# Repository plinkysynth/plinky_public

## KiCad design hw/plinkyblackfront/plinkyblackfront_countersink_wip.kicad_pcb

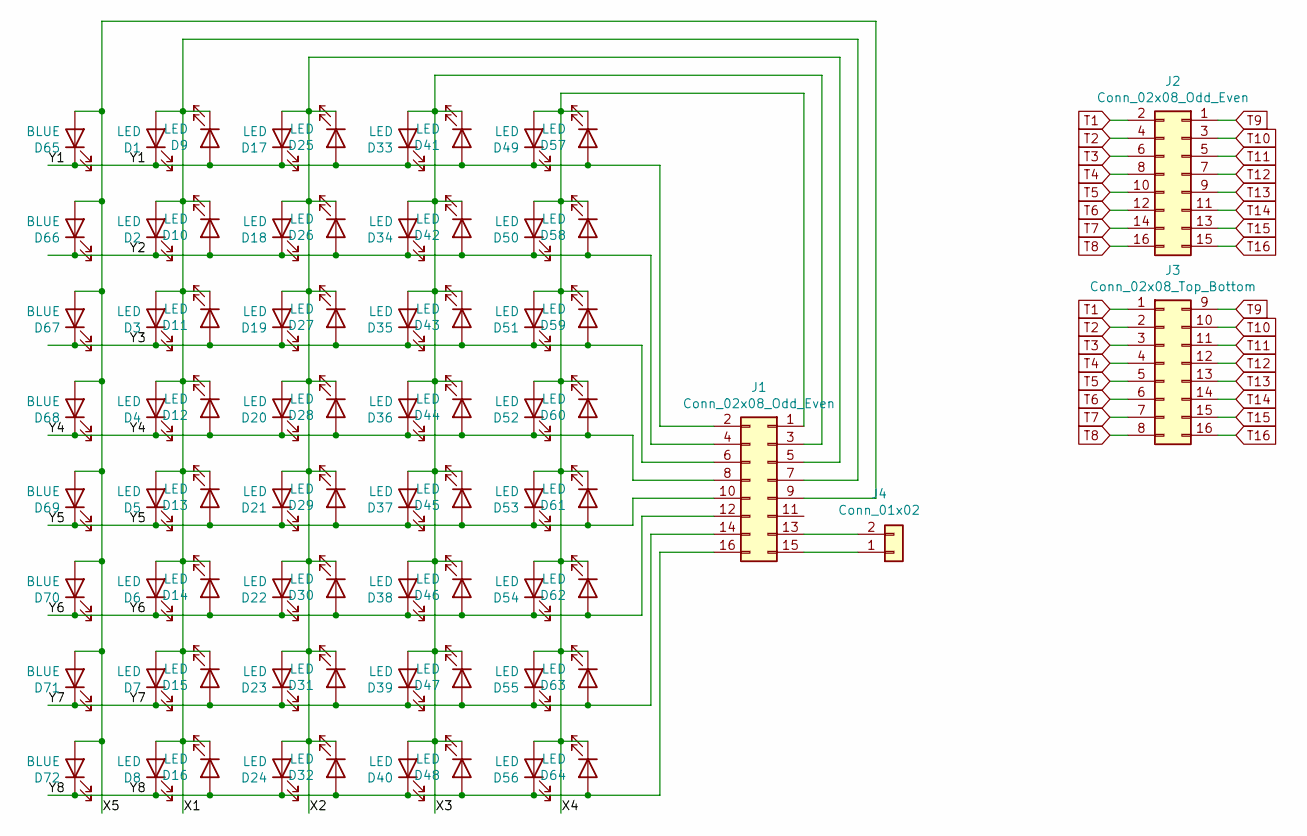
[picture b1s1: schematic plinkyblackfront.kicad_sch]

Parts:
D1, D2, D3, D4, D5, D6, D7, D8, D9, D10, D11, D12, D13, D14, D15, D16, D17, D18, D19, D20, D21, D22, D23, D24, D25, D26, D27, D28, D29, D30, D31, D32, D33, D34, D35, D36, D37, D38, D39, D40, D41, D42, D43, D44, D45, D46, D47, D48, D49, D50, D51, D52, D53, D54, D55, D56, D57, D58, D59, D60, D61, D62, D63, D64: LED; led_reverse
D65, D66, D67, D68, D69, D70, D71, D72: BLUE; led_reverse_bigger_oval
J1, J2: Conn_02x08_Odd_Even; PinHeader_2x08_P2.54mm_Vertical_SMD
J3: Conn_02x08_Top_Bottom; touchy7
J4: Conn_01x02; touchy7horiz

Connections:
/X1: D1.2 (A), D2.2 (A), D3.2 (A), D4.2 (A), D5.2 (A), D6.2 (A), D7.2 (A), D8.2 (A), D9.1 (K), D10.1 (K), D11.1 (K), D12.1 (K), D13.1 (K), D14.1 (K), D15.1 (K), D16.1 (K), J1.7
/X2: D17.2 (A), D18.2 (A), D19.2 (A), D20.2 (A), D21.2 (A), D22.2 (A), D23.2 (A), D24.2 (A), D25.1 (K), D26.1 (K), D27.1 (K), D28.1 (K), D29.1 (K), D30.1 (K), D31.1 (K), D32.1 (K), J1.5
/X3: D33.2 (A), D34.2 (A), D35.2 (A), D36.2 (A), D37.2 (A), D38.2 (A), D39.2 (A), D40.2 (A), D41.1 (K), D42.1 (K), D43.1 (K), D44.1 (K), D45.1 (K), D46.1 (K), D47.1 (K), D48.1 (K), J1.3
/X4: D49.2 (A), D50.2 (A), D51.2 (A), D52.2 (A), D53.2 (A), D54.2 (A), D55.2 (A), D56.2 (A), D57.1 (K), D58.1 (K), D59.1 (K), D60.1 (K), D61.1 (K), D62.1 (K), D63.1 (K), D64.1 (K), J1.1
/X5: D65.2 (A), D66.2 (A), D67.2 (A), D68.2 (A), D69.2 (A), D70.2 (A), D71.2 (A), D72.2 (A), J1.9
/Y1: D1.1 (K), D9.2 (A), D17.1 (K), D25.2 (A), D33.1 (K), D41.2 (A), D49.1 (K), D57.2 (A), D65.1 (K), J1.2
/Y2: D2.1 (K), D10.2 (A), D18.1 (K), D26.2 (A), D34.1 (K), D42.2 (A), D50.1 (K), D58.2 (A), D66.1 (K), J1.4
/Y3: D3.1 (K), D11.2 (A), D19.1 (K), D27.2 (A), D35.1 (K), D43.2 (A), D51.1 (K), D59.2 (A), D67.1 (K), J1.6
/Y4: D4.1 (K), D12.2 (A), D20.1 (K), D28.2 (A), D36.1 (K), D44.2 (A), D52.1 (K), D60.2 (A), D68.1 (K), J1.8
/Y5: D5.1 (K), D13.2 (A), D21.1 (K), D29.2 (A), D37.1 (K), D45.2 (A), D53.1 (K), D61.2 (A), D69.1 (K), J1.10
/Y6: D6.1 (K), D14.2 (A), D22.1 (K), D30.2 (A), D38.1 (K), D46.2 (A), D54.1 (K), D62.2 (A), D70.1 (K), J1.12
/Y7: D7.1 (K), D15.2 (A), D23.1 (K), D31.2 (A), D39.1 (K), D47.2 (A), D55.1 (K), D63.2 (A), D71.1 (K), J1.14
/Y8: D8.1 (K), D16.2 (A), D24.1 (K), D32.2 (A), D40.1 (K), D48.2 (A), D56.1 (K), D64.2 (A), D72.1 (K), J1.16
unnamed: J1.13, J4.2
unnamed: J1.15, J4.1
T1: J2.2, J3.1
T2: J2.4, J3.2
T3: J2.6, J3.3
T4: J2.8, J3.4
T5: J2.10, J3.5
T6: J2.12, J3.6
T7: J2.14, J3.7
T8: J2.16, J3.8
T9: J2.1, J3.9
T10: J2.3, J3.10
T11: J2.5, J3.11
T12: J2.7, J3.12
T13: J2.9, J3.13
T14: J2.11, J3.14
T15: J2.13, J3.15
T16: J2.15, J3.16

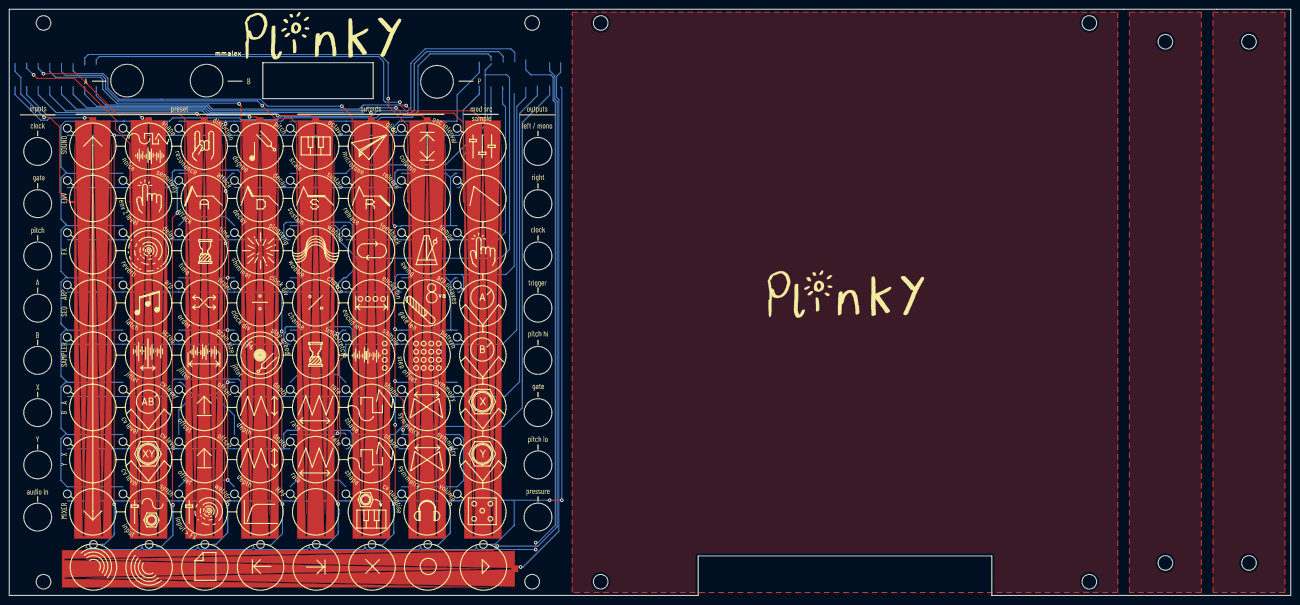
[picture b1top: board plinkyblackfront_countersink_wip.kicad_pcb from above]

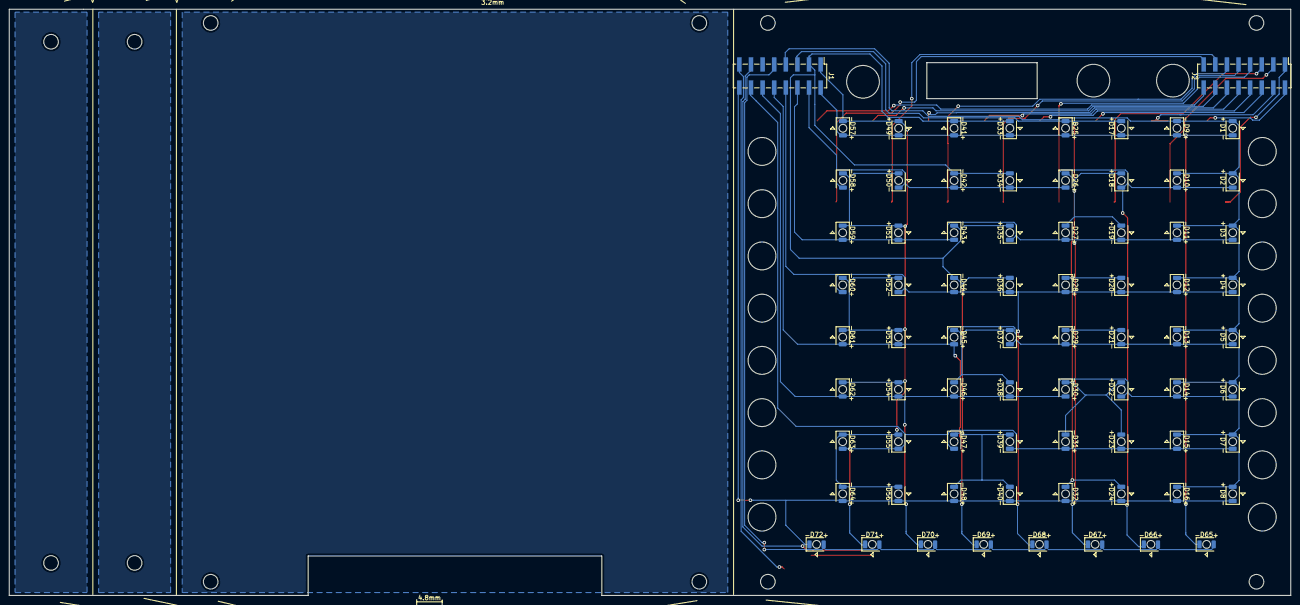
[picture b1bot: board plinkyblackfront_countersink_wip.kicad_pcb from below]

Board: 2 copper layers, 280.4 x 128.3 mm, 90 parts (74 on the bottom side), 31 nets.

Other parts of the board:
LOGO: LOGO; plinky_no_underline
LOGO#2: LOGO; plinky_no_underline
M1, M1#2, M2, M2#2, M3, M3#2, M3#3, M3#4, M3#5, M3#6, M4, M4#2: MountingHole_3.2mm_M3

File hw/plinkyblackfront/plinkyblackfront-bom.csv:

Comment,Designator,Footprint,LCSC
"LED","D1,D2,D3,D4,D5,D6,D7,D8,D9,D10,D11,D12,D13,D14,D15,D16,D17,D18,D19,D20,D21,D22,D23,D24,D25,D26,D27,D28,D29,D30,D31,D32,D33,D34,D35,D36,D37,D38,D39,D40,D41,D42,D43,D44,D45,D46,D47,D48,D49,D50,D51,D52,D53,D54,D55,D56,D57,D58,D59,D60,D61,D62,D63,D64","cap:led_reverse",""
"BLUE","D65,D66,D67,D68,D69,D70,D71,D72","cap:led_reverse",""
"Conn_02x08_Odd_Even","J1,J2","Connector_PinHeader_2.54mm:PinHeader_2x08_P2.54mm_Vertical_SMD",""
"Conn_02x08_Top_Bottom","J3","cap:touchy7",""
"Conn_01x02","J4","cap:touchy7horiz",""
